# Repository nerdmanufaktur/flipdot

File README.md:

# flipdot
Contains Code for running the flip-dot displays based on the driver pcb both from nerdmanufaktur.berlin

## Arduino 

Copy the folders from /Arduino to your local /Arduino/libraries folder and compile/upload the /Arduino/examples example Code. (Wemos for Wifi enabled ESP8266s and Arduino_HW for everything else)

The FLIPDOT library on an ESP8266 also provides an UDP-Server that listens on Port 1234 for data. It will accept DISPLAY_WIDTH*2 byte sized frames and render them immediatly.

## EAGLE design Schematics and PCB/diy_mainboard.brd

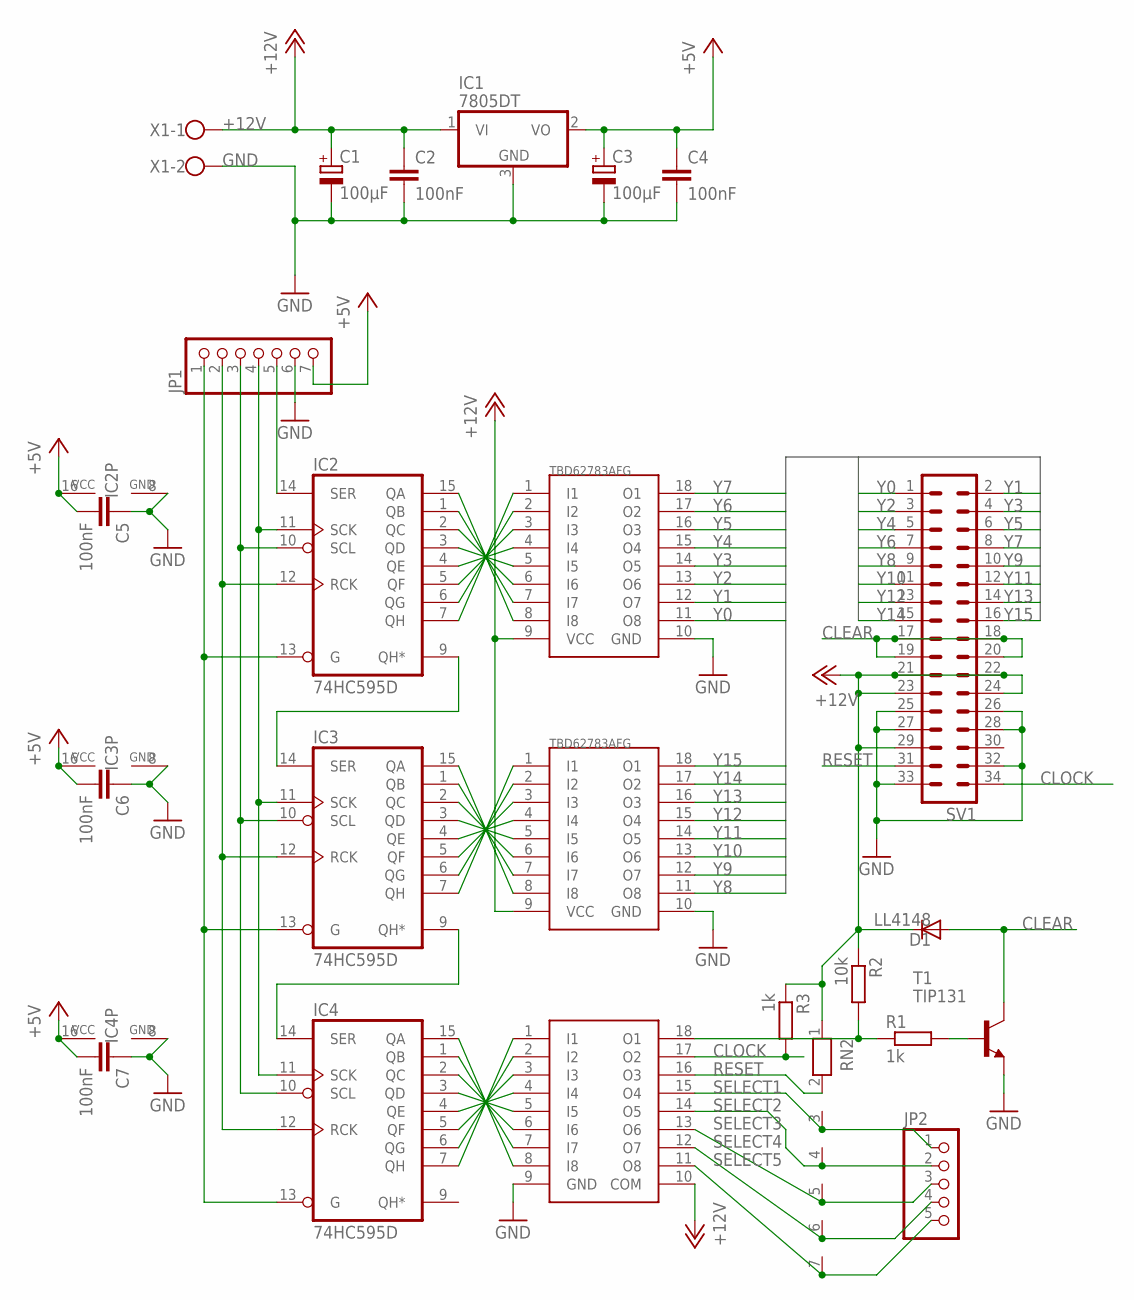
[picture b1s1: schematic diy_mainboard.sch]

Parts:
C1, C3: 100µF; 153CLV-0605; DIGIKEY 493-2203-1-ND
C2, C4, C5, C6, C7: 100nF; C0603; DIGIKEY 478-5052-1-ND
D1: LL4148; SOD80C; DIGIKEY LL4148FSCT-ND
IC1: 7805DT; TO252; DIGIKEY MC7805CDTGOS-ND
IC2, IC3, IC4: 74HC595D; SO16; DIGIKEY 568-2263-1-ND
JP1: PINHD-1X7; 1X07; DIGIKEY A101735CT-ND
JP2: PINHD-1X5; 1X05; DIGIKEY A101735CT-ND
R1, R3: 1k; R0805; DIGIKEY RMCF0805JT1K00CT-ND
R2: 10k; R0805; DIGIKEY RMCF0805JT10K0CT-ND
RN2: RN06; RN-7; DIGIKEY 4607X-101-472LF-ND
SV1: ML34; DIGIKEY AE11226-ND
T1: TIP131; TO220BV
U$1, U$2: TBD62783AFG; SO8-L; DIGIKEY TBD62783AFGELCT-ND
U$3: ULN2803; SO8-L; DIGIKEY 296-15777-1-ND
X1: W237-102

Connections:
+5V: C3.+, C4.1, C5.2, C6.2, C7.2, IC1.2 (VO), IC2.16 (VCC), IC3.16 (VCC), IC4.16 (VCC), JP1.7
+12V: C1.+, C2.1, D1.C, IC1.1 (VI), R2.1, R3.1, RN2.1, SV1.21, SV1.22, SV1.23, SV1.24, SV1.29, U$1.9 (VCC), U$2.9 (VCC), U$3.10 (COM), X1.1
CLEAR: D1.A, SV1.17, SV1.18, SV1.19, SV1.20, T1.2 (C)
CLOCK: R3.2, SV1.34, U$3.17 (O2)
GND: C1.-, C2.2, C3.-, C4.2, C5.1, C6.1, C7.1, IC1.3 (GND), IC2.8 (GND), IC3.8 (GND), IC4.8 (GND), JP1.6, SV1.25, SV1.26, SV1.27, SV1.28, SV1.32, SV1.33, T1.3 (E), U$1.10 (GND), U$2.10 (GND), U$3.9 (GND), X1.2
unnamed: IC2.15 (QA), U$1.8 (I8)
unnamed: IC2.1 (QB), U$1.7 (I7)
unnamed: IC2.2 (QC), U$1.6 (I6)
unnamed: IC2.3 (QD), U$1.5 (I5)
unnamed: IC2.4 (QE), U$1.4 (I4)
unnamed: IC2.5 (QF), U$1.3 (I3)
unnamed: IC2.6 (QG), U$1.2 (I2)
unnamed: IC2.7 (QH), U$1.1 (I1)
unnamed: IC3.15 (QA), U$2.8 (I8)
unnamed: IC3.1 (QB), U$2.7 (I7)
unnamed: IC3.2 (QC), U$2.6 (I6)
unnamed: IC3.3 (QD), U$2.5 (I5)
unnamed: IC3.4 (QE), U$2.4 (I4)
unnamed: IC3.5 (QF), U$2.3 (I3)
unnamed: IC3.6 (QG), U$2.2 (I2)
unnamed: IC3.7 (QH), U$2.1 (I1)
unnamed: IC2.9 (QH*), IC3.14 (SER)
unnamed: IC2.11 (SCK), IC3.11 (SCK), IC4.11 (SCK), JP1.4
unnamed: IC2.10 (SCL), IC3.10 (SCL), IC4.10 (SCL), JP1.3
unnamed: IC2.12 (RCK), IC3.12 (RCK), IC4.12 (RCK), JP1.2
unnamed: IC2.13 (G), IC3.13 (G), IC4.13 (G), JP1.1
unnamed: IC3.9 (QH*), IC4.14 (SER)
unnamed: IC4.15 (QA), U$3.8 (I8)
unnamed: IC4.1 (QB), U$3.7 (I7)
unnamed: IC4.2 (QC), U$3.6 (I6)
unnamed: IC4.3 (QD), U$3.5 (I5)
unnamed: IC4.4 (QE), U$3.4 (I4)
unnamed: IC4.5 (QF), U$3.3 (I3)
unnamed: IC4.6 (QG), U$3.2 (I2)
unnamed: IC4.7 (QH), U$3.1 (I1)
unnamed: R1.2, T1.1 (B)
unnamed: R1.1, R2.2, U$3.18 (O1)
unnamed: IC2.14 (SER), JP1.5
RESET: RN2.2, SV1.31, U$3.16 (O3)
SELECT1: JP2.1, RN2.3, U$3.15 (O4)
SELECT2: JP2.2, RN2.4, U$3.14 (O5)
SELECT3: JP2.3, RN2.5, U$3.13 (O6)
SELECT4: JP2.4, RN2.6, U$3.12 (O7)
SELECT5: JP2.5, RN2.7, U$3.11 (O8)
Y0: SV1.1, U$1.11 (O8)
Y1: SV1.2, U$1.12 (O7)
Y2: SV1.3, U$1.13 (O6)
Y3: SV1.4, U$1.14 (O5)
Y4: SV1.5, U$1.15 (O4)
Y5: SV1.6, U$1.16 (O3)
Y6: SV1.7, U$1.17 (O2)
Y7: SV1.8, U$1.18 (O1)
Y8: SV1.9, U$2.11 (O8)
Y9: SV1.10, U$2.12 (O7)
Y10: SV1.11, U$2.13 (O6)
Y11: SV1.12, U$2.14 (O5)
Y12: SV1.13, U$2.15 (O4)
Y13: SV1.14, U$2.16 (O3)
Y14: SV1.15, U$2.17 (O2)
Y15: SV1.16, U$2.18 (O1)

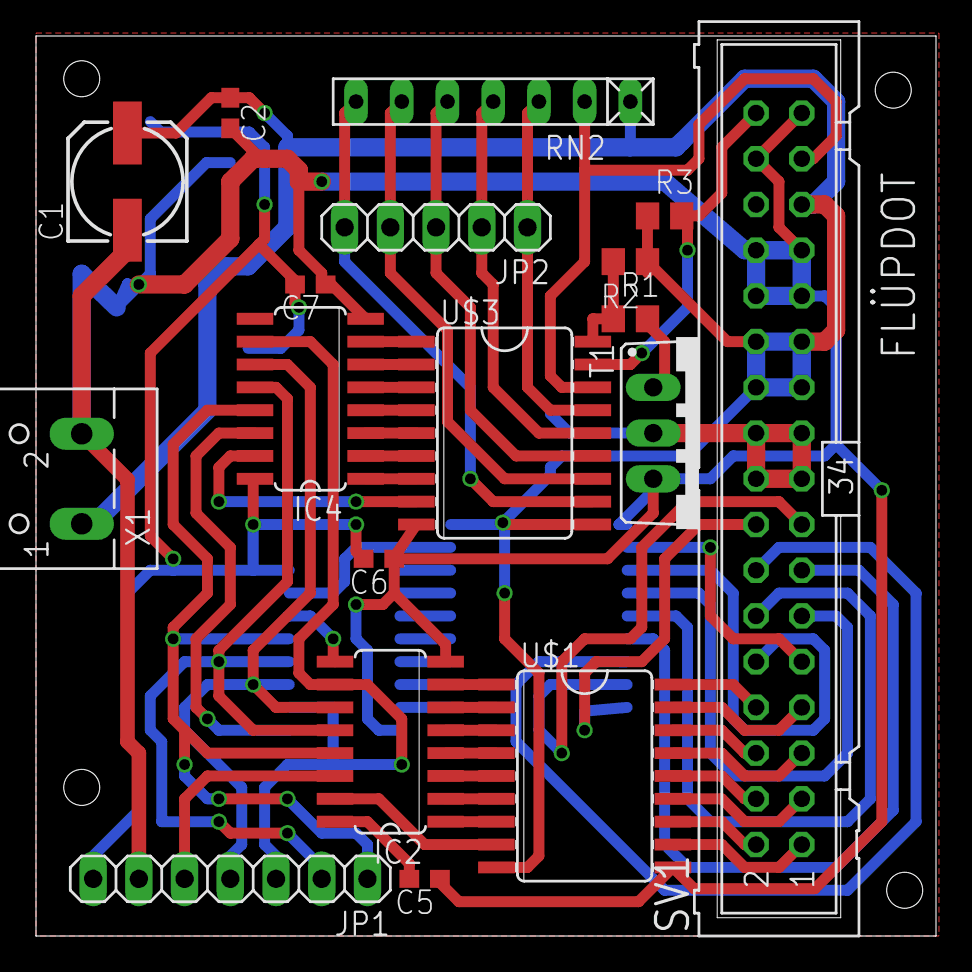
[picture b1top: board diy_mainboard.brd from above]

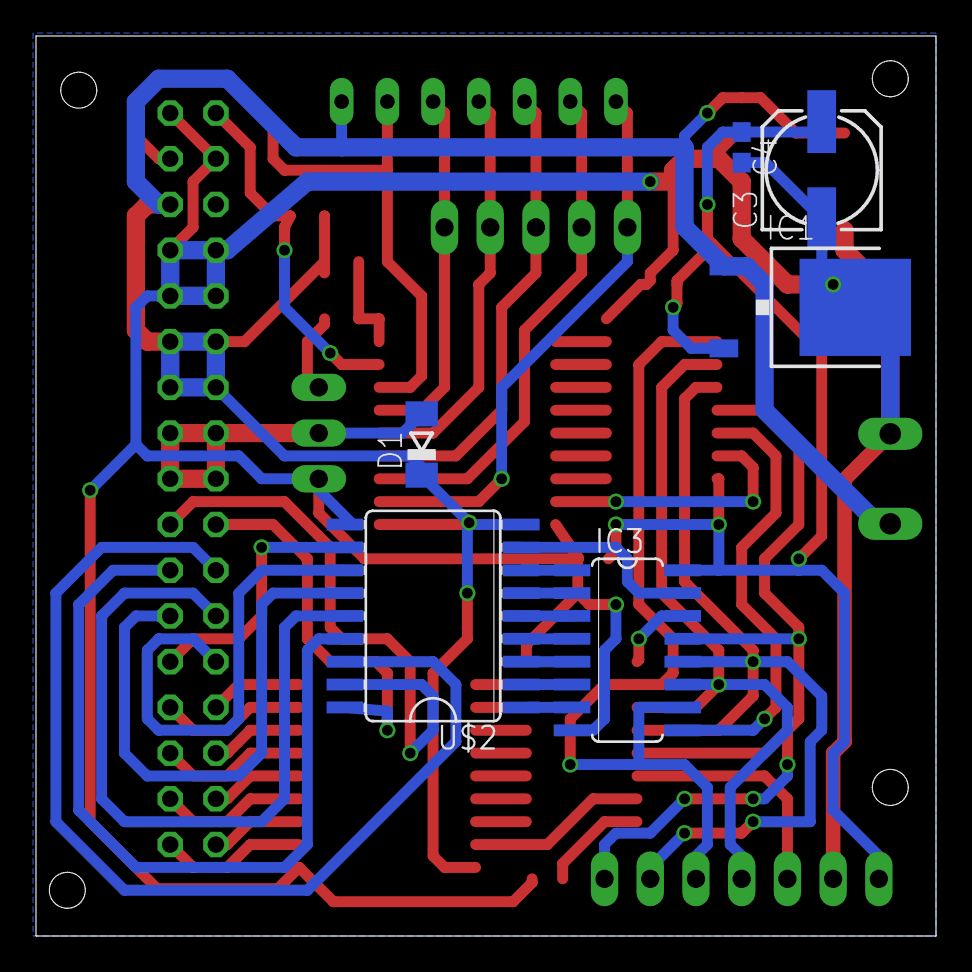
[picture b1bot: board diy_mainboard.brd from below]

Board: 2 copper layers, 50.0 x 50.0 mm, 24 parts (6 on the bottom side), 60 nets.

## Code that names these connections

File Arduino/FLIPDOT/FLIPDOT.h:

// - - - - -
// FLIPDOT - A Arduino library for controlling an Annex/AEG flip dot display
// FLIPDOT.cpp: Library implementation file
//
// Copyright (C) 2016 fluepke, kryptokommunist <fabian.luepke<at>student.hpi.de>,<marcus.ding<at>student.hpi.de>
// This work is licensed under a GNU style license.
//
// Last change: kryptokommunist
//
// Documentation and samples are available at https://github.com/nerdmanufaktur/flipdot
// - - - - -

// ---- Options ----
//flip screen? comment out for deactivating and vice versa
#define TURNDISPLAY_180_DEGREES

//comment out to disable debugging information via Serial
//#define DBG

#include <inttypes.h>
#include <Arduino.h>
#include <SPI.h>
#include "bitreverse_table.h"

//Arduino hw vs. ESP8266
#if defined(ESP8266)
  #include "font_non_arduino_hw.h"
  #include "font8x8_non_arduino_hw.h"
  #include <ESP8266WiFi.h>
  #include "ESPAsyncUDP.h"
  #if defined(ARDUINO_ESP8266_WEMOS_D1MINI)
    #define SHIFT_OE_PIN D2
    #define SHIFT_RCK_PIN D3
  #else
    #define SHIFT_OE_PIN 9
    #define SHIFT_RCK_PIN 3
  #endif
#else
    #include "font.h"
    #include "font8x8.h"
    #define SHIFT_OE_PIN 9
    #define SHIFT_RCK_PIN 3
#endif

#ifndef FLIPDOT_H
#define FLIPDOT_H

// ---- Constants/Preprocessor functions ----

#define UDP_PORT_FRAME_SERVER 1234

#define CHAR_WIDTH 16
#define CHAR_HEIGHT 16
#define CHAR_OFFSET CHAR_WIDTH - 6
#define CHAR_WIDTH_SMALL 8
#define CHAR_HEIGHT_SMALL 8
#define CHAR_OFFSET_SMALL CHAR_WIDTH_SMALL - 3
#define DEFAULT_SCROLL_DELAY_MILLISECONDS 0
#define DEFAULT_SCROLL_X_OFFSET DISPLAY_WIDTH
#define DEFAULT_SMALL_Y_OFFSET 4
#define RENDER_STRING_DEFAULT_X_OFFSET 0
#define DEFAULT_ZEROING_SETTING ZERO_LOCALLY

//#define PANEL_CONFIGURATION single: [1] = {25} up to full: [5] = {25,25,20,20,25}
//each entry being the width of the iths panel (either 20 or 25), change arraysize as well!
#define PANEL_CONFIGURATION [5] = {25,25,20,20,25}
#define DISPLAY_WIDTH 115 //also adjust width!

#define MAX_NUMBER_OF_PANELS 5
#define COL_HEIGHT 16

// Positions in Control Buffer
// |     7    |     6    |     5    |     4    |     3    |     2    |     1    |     0
// |  CLEAR   |   CLOCK  |   RESET  | SELECT 1 | SELECT 2 | SELECT 3 | SELECT 4 | SELECT 5 |

#define CLEAR 7
//signal is inverted
#define CLOCK 6
//signal is inverted
#define RESET 5
#define SELECT1 4
#define SELECT2 3
#define SELECT3 2
#define SELECT4 1
#define SELECT5 0

#define ALL_COLUMN_PIXELS_ON 0b1111111111111111

#if defined(DBG)
  #include <bitset>
  #define DBG_OUTPUT_PORT(data) Serial.print(data);
  #define DBG_OUTPUT_PORT_NL(data) Serial.println(data);
#else
  #define DBG_OUTPUT_PORT(data)
  #define DBG_OUTPUT_PORT_NL(data)
#endif

//sets the control bits in controlBuffer, select for all pins is 1 and for pin select_number it is set to select_value
#define setControlBits(clr,clk,rst,select_value, select_number) controlBuffer =  (clr << CLEAR) | (clk << CLOCK) | (rst << RESET) | (1 << SELECT1) | \
  (1 << SELECT2) | (1 << SELECT3) | (1 << SELECT4) | (1 << SELECT5);\
  /*catch if selected pin is set (its 0 because of inverted transistor output)*/\
  if(select_value == 0){\
      controlBuffer &=  -1 ^ (1 << select_number);\
  }

  //function call is too slow and the compiler not clever enough, therefore we use a preprocessor fake function
  #define initializePanel(select_pin)  columnBuffer = 0;\
    setControlBits(0,1,0,1,select_pin)\
    writeToRegisters();\
    digitalWrite(SHIFT_OE_PIN, LOW);\
    setControlBits(1,1,0,1,select_pin)\
    columnBuffer = ALL_COLUMN_PIXELS_ON;\
    writeToRegisters();\
    delayMicroseconds(200);\
    setControlBits(0,1,0,1,select_pin)\
    columnBuffer = 0;\
    writeToRegisters();\
    delayMicroseconds(100);\
    setControlBits(0,1,1,0,select_pin)\
    writeToRegisters();\
    delayMicroseconds(200);\
    setControlBits(1,0,1,0,select_pin)\
    writeToRegisters();\
    delayMicroseconds(20);\
    setControlBits(1,1,1,1,select_pin)\
    writeToRegisters();\
    delayMicroseconds(30);\
    setControlBits(0,1,1,1,select_pin)\
    writeToRegisters();

  //function call is too slow and the compiler not clever enough, therefore we use a preprocessor fake function
  #define writeToNewColumn(data,select_pin,time) delayMicroseconds(time);\
      setControlBits(1,1,1,1,select_pin)\
      writeToRegisters();\
      setControlBits(1,0,1,1,select_pin)\
      writeToRegisters();\
      setControlBits(1,1,1,1,select_pin)\
      columnBuffer = data;\
      writeToRegisters();\
      delayMicroseconds(time);\
      columnBuffer = 0;\
      setControlBits(0,1,1,1,select_pin)\
      writeToRegisters();\
      setControlBits(1,0,1,1,select_pin)\
      writeToRegisters();\
      setControlBits(1,1,1,1,select_pin)\
      writeToRegisters();\
      setControlBits(0,1,1,1,select_pin)\
      writeToRegisters();

// ---- Methods ----

class FLIPDOT {

public:
  //ZERO_ALL => zero the entire buffer before rendering
  //ZERO_LOCALLY => zero the entire column if something is rendered on it, leave remaining columns as before
  //ZERO_NONE => don't zero anything, just merge the previous pixel state with the additional pixels
  typedef enum { ZERO_ALL,ZERO_LOCALLY,ZERO_NONE } ZeroOptions;
  typedef enum { NONE, STEP_THROUGH_PIXEL_CHANGES } Animation;
  FLIPDOT();
  void init();
  void render_frame(uint16_t frame[DISPLAY_WIDTH]);
  void render_to_panel(uint16_t* frame, uint8_t panel_index);
  void render_string(const char *s, int x_offset = RENDER_STRING_DEFAULT_X_OFFSET, ZeroOptions zero_buffer = DEFAULT_ZEROING_SETTING);
  void render_string_small(const char* str, int x_offset = RENDER_STRING_DEFAULT_X_OFFSET, short y_offset = DEFAULT_SMALL_Y_OFFSET, ZeroOptions zero_buffer = DEFAULT_ZEROING_SETTING);
  void scroll_string(const char *s, int x_offset = DEFAULT_SCROLL_X_OFFSET, int millis_delay = DEFAULT_SCROLL_DELAY_MILLISECONDS, ZeroOptions zero_buffer = DEFAULT_ZEROING_SETTING);
  void scroll_string_small(const char *s, int x_offset = DEFAULT_SCROLL_X_OFFSET, int millis_delay = DEFAULT_SCROLL_DELAY_MILLISECONDS, short y_offset = DEFAULT_SMALL_Y_OFFSET, ZeroOptions zero_buffer = DEFAULT_ZEROING_SETTING);
  void render_char_to_buffer(char c, short x, ZeroOptions zero_buffer);
  void render_char_to_buffer_small(char c, int x, short y_offset, ZeroOptions zero_buffer);
  void merge_columns(uint16_t* dest_column, const uint16_t* src_column) ;
  void render_internal_framebuffer();
  void render_internal_framebuffer_diff_step_animation();
  void draw_in_internal_framebuffer(int val, uint8_t x, uint8_t y);
  void draw_byte_in_internal_framebuffer(uint8_t val, uint8_t x, uint8_t y);
  void all_off();
  void all_on();
  void start_udp_server();
  void stop_udp_server();
  bool received_udp_frame_recently();
  void reset_internal_framebuffer();
  uint8_t read_internal_framebuffer(uint8_t x, uint8_t y);
  uint8_t get_panel_column_offset(uint8_t panel_index);
private:
  uint8_t panel_configuration PANEL_CONFIGURATION;
  uint8_t select_pin_mapping[MAX_NUMBER_OF_PANELS] = {SELECT1,SELECT2,SELECT3,SELECT4,SELECT5};
  uint8_t number_of_panels;
  uint16_t frame_buff[DISPLAY_WIDTH] = {0}; //frame buffer (for super fancy diffing etc.)
  uint16_t last_frame_buff[DISPLAY_WIDTH] = {0};
  uint16_t columnBuffer = 0; //holds data of current column pixel data
  byte controlBuffer = 0; //holds data of current control bits (clear, clock, reset, select 1, ... , select 5)
  bool col_changed[DISPLAY_WIDTH] = {false}; //indicates if column changed since last rendering
  void writeToRegisters();
  void render_frame_no_yield(uint16_t frame[DISPLAY_WIDTH]);
  void render_internal_framebuffer_no_yield();
  void set_frame_buff(int val);
  bool frame_buff_changed_for_panel(uint8_t panel_index);
  uint16_t font_column_rendering_convert_endianess(uint16_t current_font_column, short y_offset);

  //only for esp8266
  #if defined(ESP8266)
    AsyncUDP udp;
    long time_since_last_udp_frame;
    void process_udp_frame(uint8_t* data, size_t length);
  #endif
};

#endif

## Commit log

2017-03-23 create FLIPDOT::initialize()
2017-03-23 improve perfomance of FLIPDOT::scroll_string()
2017-03-23 add FLIPDOT::all_off() and FLIPDOT::render_internal_framebuffer() and perfomance improvements
2017-03-23 add small fonts
2017-03-23 add more fonts
2017-03-23 modify timings to reduce artefacts
2017-03-24 add buffer diffing and more options for rendering
2017-03-25 add support for up to 5 display boards
2017-03-25 add diffing of panels for faster rendering and add pixel drawing
2017-03-25 refine drawing method
2017-03-25 refine drawing method in library
2017-03-25 add functionality of rendering multiple strings on board
2017-03-27 add support for ESP8266
2017-03-27 add libraries for more efficient time tracking via ntp
2017-03-28 update README and Arduino code
2017-03-29 add asynchronous UDP server to receive frames over network
2017-03-29 now really adding asynchronous UDP server to receive frames over network
2017-03-30 add display turning functionality and better debugging info
2017-03-30 fix exception due to calling yield when heap is full
2017-03-30 add bitreverse table
2017-03-30 add travis ci
2017-03-30 ci test
2017-03-30 split examples into esp8266 and non wifi Arduino hw
2017-03-30 fix bug in travis ci yml
2017-03-30 fix bug with correctly detecting usage of ESP8266
2017-03-30 fix bug concerning usage of other boards than wemos
2017-04-03 Added schematics and pcb layout
2017-05-08 Improve code
2017-05-08 Fix bugs and add better demo program
2017-05-08 Improve Demo Code
2017-05-08 Fix compilation erros
2017-05-08 Edit travis.yml
2017-05-08 Fix Syntax issues + Edit travis.yml
2017-05-08 Fix Syntax issues
2017-06-01 Massive speed increase by skipping unchanged columns
2017-06-09 Faster flipping
